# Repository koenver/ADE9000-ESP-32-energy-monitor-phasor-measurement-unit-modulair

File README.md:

# **ADE9000 ESP-32 energy-monitor / phasor-measurement-unit modulair**<br/>

*Prototype version of an Energy Measurement / Phasor Measurement unit with modulair interface modules*<br/>

**Specs:**<br/>
* ESP-32 processor (with double SPI and multicore, multi-tasking) and Wifi<br/> 
* Galvanic seperation with ADUM chips <br/>
* ADE9000 3 phase Energy Measurement IC , version for CT (5VA) or <br/>
        rogowski (0.1mV/A), 8kHz wavebuffering , harmonics analyses and <br/>
        event processing for 50Hz , 230V 3 phase Energy systems <br/>
* Module 1 slot: 485 interface / lorawan 868 Mhz/ Ethernet lan8720 (waveshare)<br/>
        
* Module 2 slot: Ublox GPS / DS3232 RTC<br/> 
* Expansion board: 485 interface, 2x 24lc512, mcp23017, ds2482, mcp4725,BME680<br/> 
        so 4 DI (opto), 4 DO (opto), 1-wire , temp, humidity, voc, air-pressure, <br/>
	AD en DA inputs and extra flash <br/>
* Optional I2C display  (SED1306 or H35B-I)<br/>
* future development:  security TLS1.3, module 2 with NB-Iot-LTE-M (Ublox)<br/> 
* Arduino IDE , in RTOS , C++ Language <br/>
<br/>

#### *Now in testing phase -> so only use parts which I confirmed status tested*<br/>
#### *better wait till new PCB's are published, instead of using the manual re-wiring*<br/>
*Software will be open source. (New) soft- and hardware which is based on this*<br/> 
*project and used by others, have the obligation of open source publishing*<br/> 
*at Github*<br/>

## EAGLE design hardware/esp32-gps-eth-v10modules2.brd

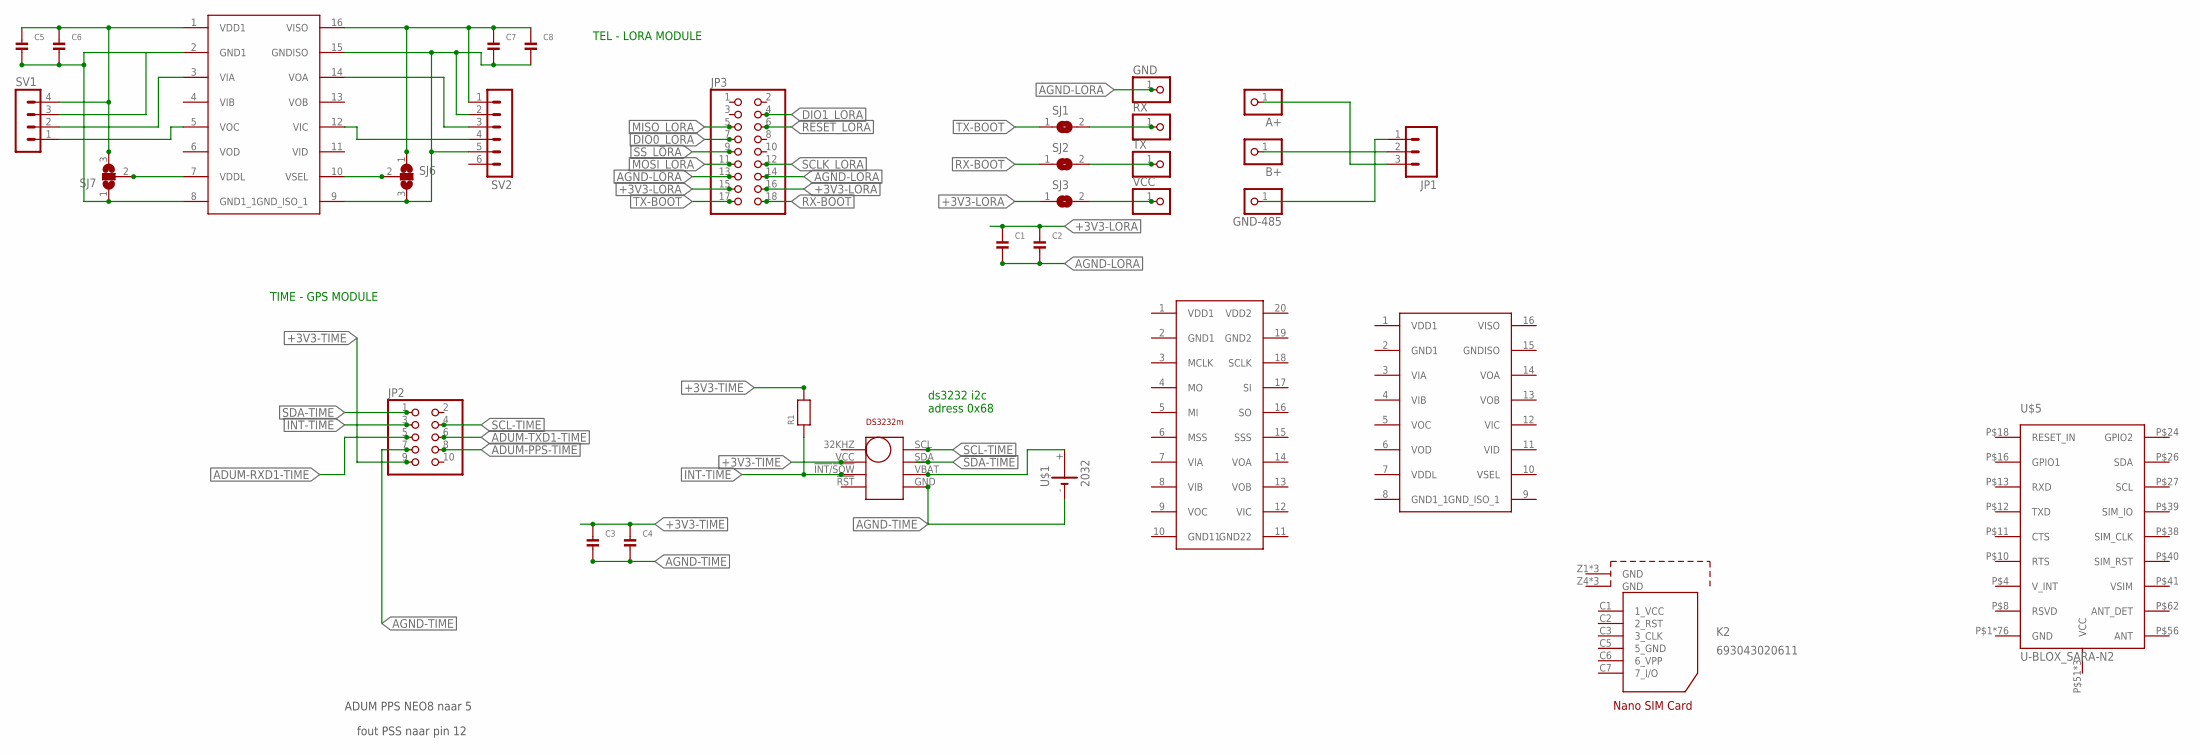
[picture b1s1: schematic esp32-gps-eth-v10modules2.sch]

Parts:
A+: PINHD-1X1CB; 1X01-CLEANBIG
ADUM4151: ADUM4151; SOIC20R
B+: PINHD-1X1CB; 1X01-CLEANBIG
C1, C2, C3, C4, C5, C6, C7, C8: CAP_CERAMIC0805; 0805
GND: PINHD-1X1CB; 1X01-CLEANBIG
GND-485: PINHD-1X1CB; 1X01-CLEANBIG
JP1: M03SCREW; SCREWTERMINAL-3.5MM-3
JP2: PINHD-2X5/90; 2X05/90
JP3: PINHD-2X9/90; 2X09/90
K2: 693043020611
R1: RESISTOR0805; 0805
RX: PINHD-1X1CB; 1X01-CLEANBIG
SJ1, SJ2, SJ3: SOLDERJUMPERREFLOW; SOLDERJUMPER_REFLOW
SJ6, SJ7: SJ2W; SJ_2
SV1: MA04-1
SV2: MA06-1
TX: PINHD-1X1CB; 1X01-CLEANBIG
U$1: 2032; KZH20SMD
U$2, U$3: ADUM6402; SOIC16R
U$4: DS3232M; SOIC8
U$5: U-BLOX_SARA-N2; SARA-N2
VCC: PINHD-1X1CB; 1X01-CLEANBIG

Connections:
+3V3-LORA: C1.1, C2.1, JP3.15, JP3.16, SJ3.1
+3V3-TIME: C3.1, C4.1, JP2.9, R1.2, U$4.VCC
ADUM-PPS-TIME: JP2.8
ADUM-RXD1-TIME: JP2.5
ADUM-TXD1-TIME: JP2.6
AGND-LORA: C1.2, C2.2, GND.1, JP3.13, JP3.14
AGND-TIME: C3.2, C4.2, JP2.7, U$1.-, U$4.GND
DIO0_LORA: JP3.7
DIO1_LORA: JP3.4
GND: U$5.P$1 (GND), U$5.P$2 (GND), U$5.P$3 (GND), U$5.P$5 (GND), U$5.P$6 (GND), U$5.P$7 (GND), U$5.P$9 (GND), U$5.P$14 (GND), U$5.P$15 (GND), U$5.P$17 (GND), U$5.P$19 (GND), U$5.P$20 (GND), U$5.P$21 (GND), U$5.P$22 (GND), U$5.P$23 (GND), U$5.P$25 (GND), U$5.P$28 (GND), U$5.P$29 (GND), U$5.P$30 (GND), U$5.P$31 (GND), U$5.P$32 (GND), U$5.P$33 (GND), U$5.P$34 (GND), U$5.P$35 (GND), U$5.P$36 (GND), U$5.P$37 (GND), U$5.P$42 (GND), U$5.P$43 (GND), U$5.P$44 (GND), U$5.P$45 (GND), U$5.P$46 (GND), U$5.P$47 (GND), U$5.P$48 (GND), U$5.P$49 (GND), U$5.P$50 (GND), U$5.P$54 (GND), U$5.P$55 (GND), U$5.P$57 (GND), U$5.P$58 (GND), U$5.P$59 (GND), U$5.P$60 (GND), U$5.P$61 (GND), U$5.P$63 (GND), U$5.P$64 (GND), U$5.P$65 (GND), U$5.P$66 (GND), U$5.P$67 (GND), U$5.P$68 (GND), U$5.P$69 (GND), U$5.P$70 (GND), U$5.P$71 (GND), U$5.P$72 (GND), U$5.P$73 (GND), U$5.P$74 (GND), U$5.P$75 (GND), U$5.P$76 (GND), U$5.P$77 (GND), U$5.P$78 (GND), U$5.P$79 (GND), U$5.P$80 (GND), U$5.P$81 (GND), U$5.P$82 (GND), U$5.P$83 (GND), U$5.P$84 (GND), U$5.P$85 (GND), U$5.P$86 (GND), U$5.P$87 (GND), U$5.P$88 (GND), U$5.P$89 (GND), U$5.P$90 (GND), U$5.P$91 (GND), U$5.P$92 (GND), U$5.P$93 (GND), U$5.P$94 (GND), U$5.P$95 (GND), U$5.P$96 (GND)
GND-PROG1: C5.2, C6.2, SJ7.1, U$3.8 (GND1_1)
GND-PROG2: C7.2, C8.2, SJ6.3, SV2.2, SV2.5, U$3.9 (GND_ISO_1), U$3.15 (GNDISO)
INT-TIME: JP2.3, R1.1, U$4.!INT/!!SQW
MISO_LORA: JP3.5
MOSI_LORA: JP3.11
unnamed: A+.1, JP1.3
unnamed: B+.1, JP1.2
unnamed: GND-485.1, JP1.1
unnamed: RX.1, SJ1.2
unnamed: U$1.+, U$4.VBAT
unnamed: SJ2.2, TX.1
unnamed: SJ3.2, VCC.1
unnamed: SV1.1, U$3.5 (VOC)
unnamed: SV1.3, U$3.2 (GND1)
unnamed: SV1.2, U$3.3 (VIA)
unnamed: SV2.3, U$3.14 (VOA)
unnamed: SV2.4, U$3.12 (VIC)
unnamed: SJ7.2, U$3.7 (VDDL)
unnamed: SJ6.2, U$3.10 (VSEL)
RESET_LORA: JP3.6
RX-BOOT: JP3.18, SJ2.1
SCL-TIME: JP2.4, U$4.SCL
SCLK_LORA: JP3.12
SDA-TIME: JP2.1, U$4.SDA
SS_LORA: JP3.9
TX-BOOT: JP3.17, SJ1.1
VCC: U$5.P$51 (VCC), U$5.P$52 (VCC), U$5.P$53 (VCC)
VCC2-PROG: C7.1, C8.1, SJ6.1, SV2.1, U$3.16 (VISO)
VCC-PROG: C5.1, C6.1, SJ7.3, SV1.4, U$3.1 (VDD1)

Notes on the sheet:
ADUM PPS NEO8 naar 5
fout PSS naar pin 12
ds3232 i2c adress 0x68
TEL - LORA MODULE
TIME - GPS MODULE

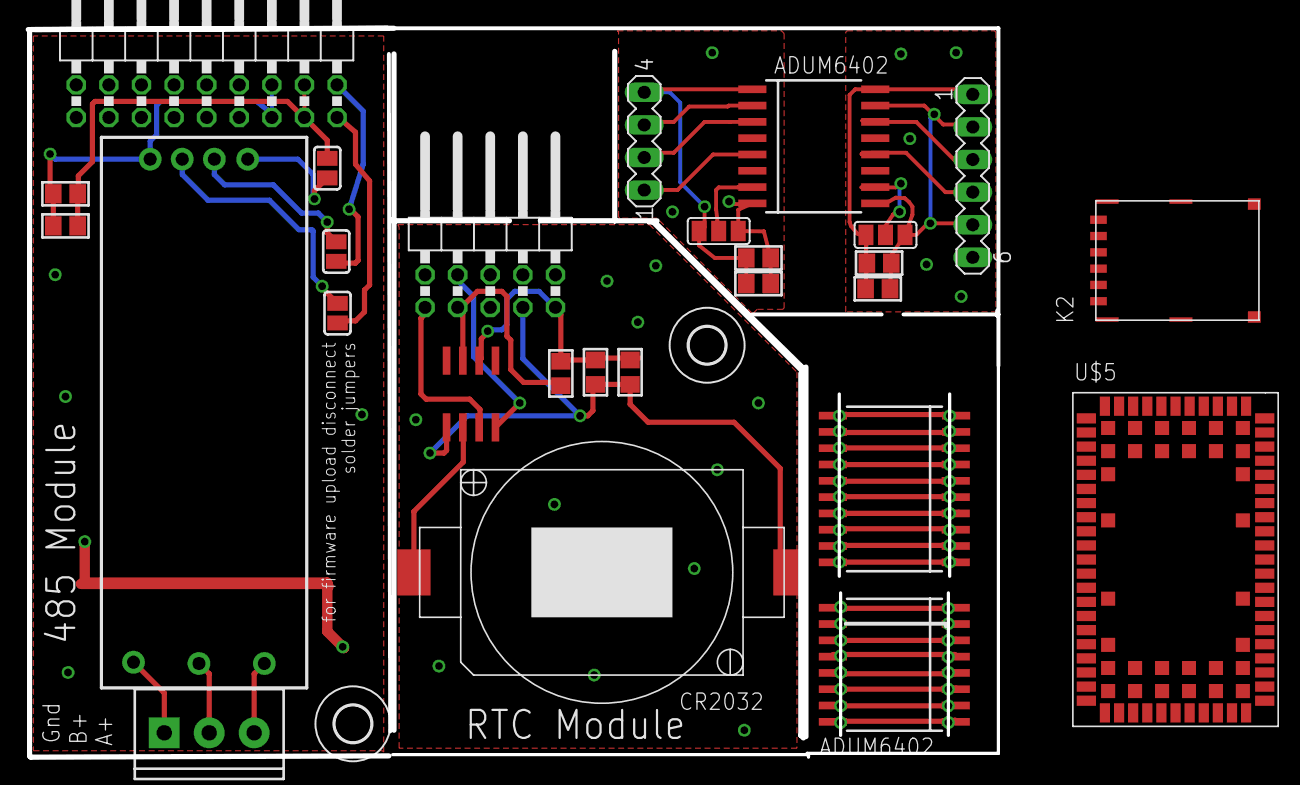
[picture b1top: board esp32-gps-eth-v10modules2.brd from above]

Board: 2 copper layers, 75.6 x 56.8 mm, 35 parts (0 on the bottom side), 29 nets.

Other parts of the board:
U$7, U$8: 2,8

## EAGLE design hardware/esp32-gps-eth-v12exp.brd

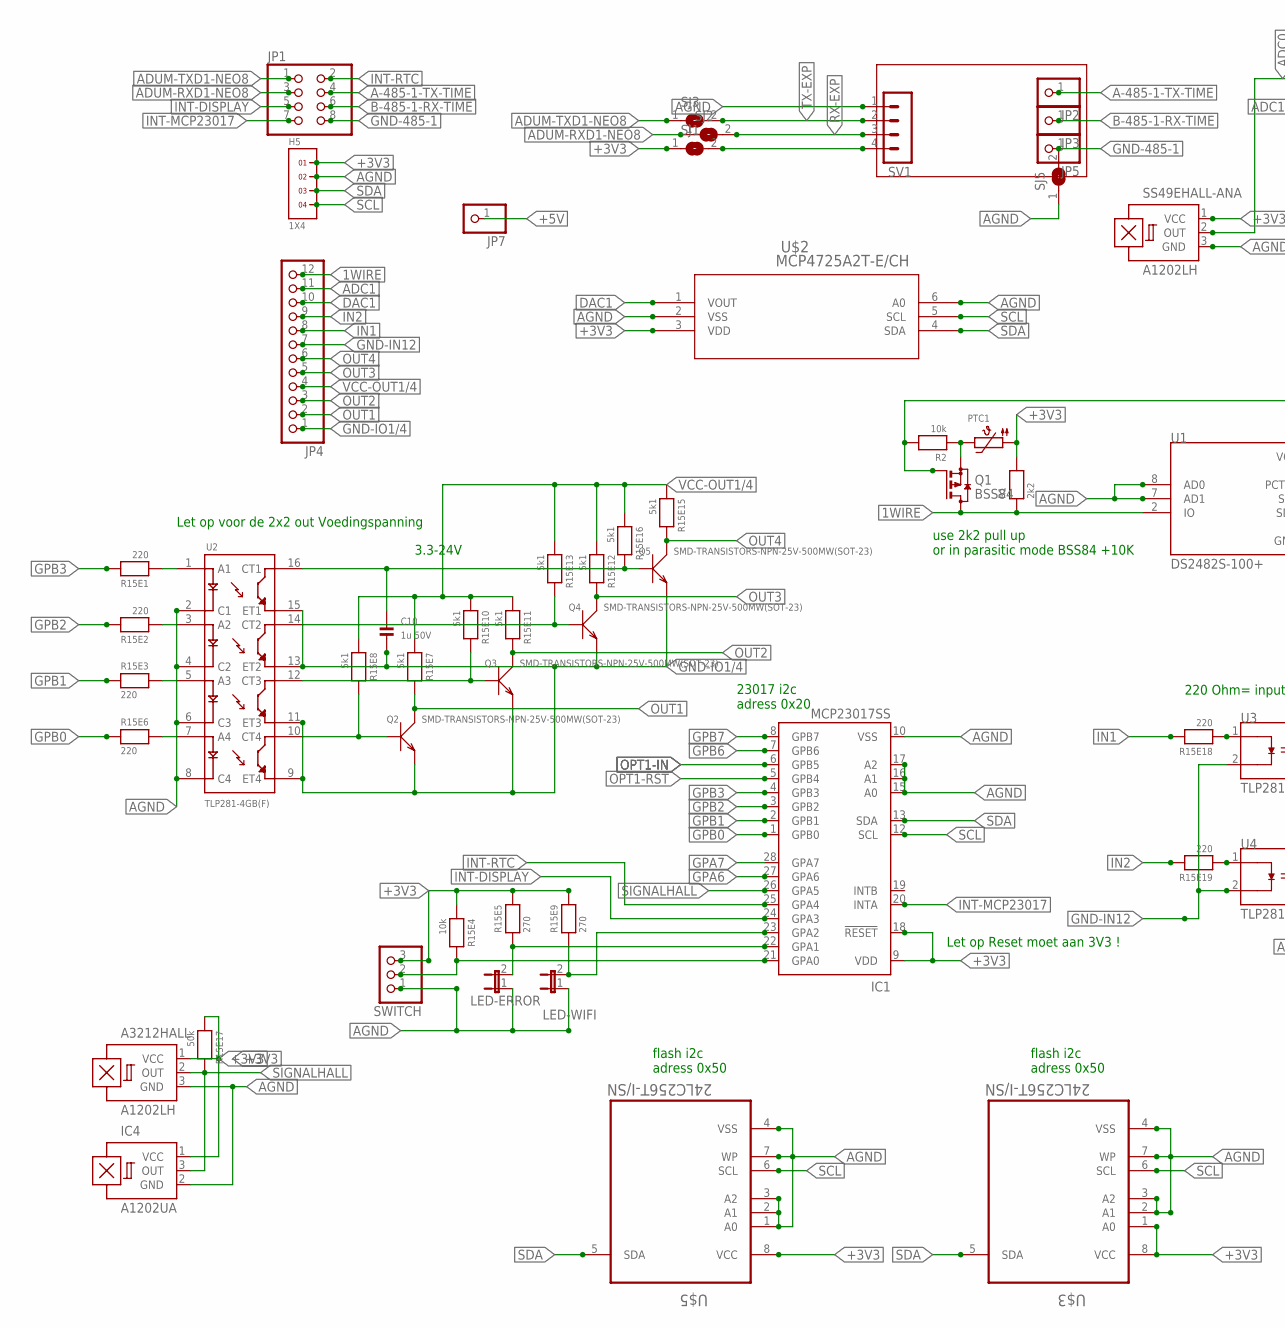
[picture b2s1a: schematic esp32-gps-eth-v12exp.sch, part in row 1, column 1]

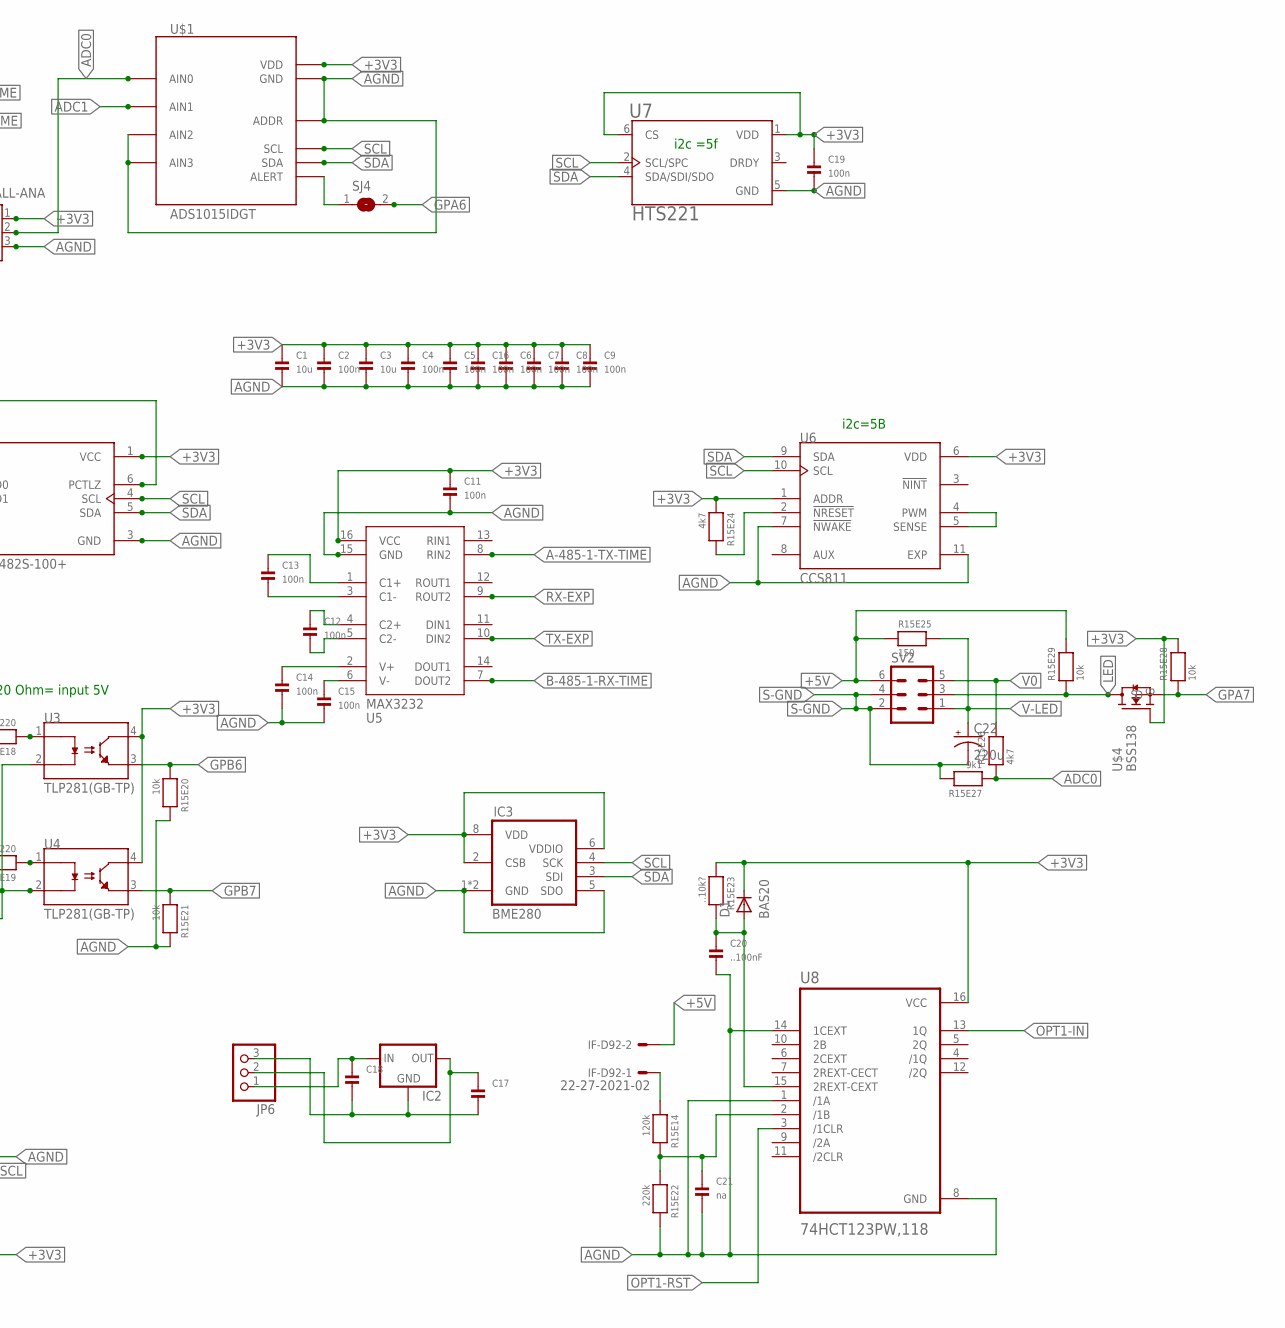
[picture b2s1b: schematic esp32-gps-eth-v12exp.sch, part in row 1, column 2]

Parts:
A3212HALL: A1202LH; SOT23-W
C1, C3: 10u; 0805
C2, C4, C5, C6, C7, C8, C9, C11, C12, C13, C14, C15, C16, C19: 100n; 0805
C10: 1u 50V; 0805
C17, C18: CAP_CERAMIC0805; 0805
C20: ..100nF; 0805
C21: na; 0805
C22: 220u; 153CLV-0605
D1: BAS20; SOT23
H5: 1X4
IC1: MCP23017SS; SSOP28
IC2: LM1117TO263; TO263
IC3: BME280
IC4: A1202UA; SIP3-UA
IF-D92: 22-27-2021-02; 6410-02
JP1: PINHD-2X4; 2X04
JP2, JP3, JP5, JP7: PINHD-1X1; 1X01
JP4: PINHD-1X12; 1X12
JP6: PINHD-1X3; 1X03
LED-ERROR: JP1E; JP1
LED-WIFI: JP1E; JP1
PTC1: PTC1206; 1206
Q1: BSS84; SOT23
Q2, Q3, Q4, Q5: SMD-TRANSISTORS-NPN-25V-500MW(SOT-23); SOT-23
R1: 2k2; 0805
R2: 10k; 0805
R15E1, R15E2, R15E3, R15E6, R15E18, R15E19: 220; _0805
R15E4, R15E20, R15E21, R15E28, R15E29: 10k; _0805
R15E5, R15E9: 270; _0805
R15E7, R15E8, R15E10, R15E11, R15E12, R15E13, R15E15, R15E16: 5k1; _0805
R15E14: 120k; _0805
R15E17: 50k; _0805
R15E22: 220k; _0805
R15E23: ..10k?; _0805
R15E24, R15E26: 4k7; _0805
R15E25: 150; _0805
R15E27: 9k1; _0805
SJ1, SJ2, SJ3, SJ4, SJ5: SJ
SS49EHALL-ANA: A1202LH; SOT23-W
SV1: MA04-1
SV2: MA03-2
SWITCH: PINHD-1X3; 1X03
U1: DS2482S-100+; SOIC127P600X175-8N
U2: TLP281-4GB(F); SOIC127P700X210-16N
U3, U4: TLP281(GB-TP); SOIC127P700X210-4N
U5: MAX3232; SO16
U6: CCS811; SON60P270X400X110-11N
U7: HTS221; XDCR_HTS221
U8: 74HCT123PW,118; SOP65P640X110-16N
U$1: ADS1015IDGT; MSOP10_0.5
U$2: MCP4725A2T-E/CH; SOT-23-6_MC
U$3, U$5: 24LC256T-I/SN; SOIC127P600X175-8N
U$4: BSS138

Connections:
1WIRE: JP4.12, Q1.3 (D), R1.1, U1.2 (IO)
5VIN: C18.1, IC2.3 (IN), JP6.1
+3V3: A3212HALL.1 (VCC), C1.1, C2.1, C3.1, C4.1, C5.1, C6.1, C7.1, C8.1, C9.1, C11.1, C16.1, C19.1, D1.3 (K), H5.1, IC1.9 (VDD), IC1.18 (!RESET), IC3.2 (CSB), IC3.6 (VDDIO), IC3.8 (VDD), IC4.1 (VCC), PTC1.1, R1.2, R15E4.1, R15E5.2, R15E9.2, R15E17.1, R15E23.1, R15E24.1, R15E28.2, SJ1.1, SS49EHALL-ANA.1 (VCC), SWITCH.3, U1.1 (VCC), U3.4 (COLLECTOR), U4.4 (COLLECTOR), U5.16 (VCC), U6.1 (ADDR), U6.6 (VDD), U7.1 (VDD), U7.6 (CS), U8.16 (VCC), U$1.8 (VDD), U$2.3 (VDD), U$3.1 (A0), U$3.8 (VCC), U$4.G, U$5.8 (VCC)
+5V: IF-D92.2, JP7.1, R15E25.1, R15E29.2, SV2.6
A-485-1-TX-TIME: JP1.4, JP2.1, U5.8 (RIN2)
ADC0: R15E26.1, R15E27.1, SS49EHALL-ANA.2 (OUT), U$1.4 (AIN0)
ADC1: JP4.11, U$1.5 (AIN1)
ADUM-RXD1-NEO8: JP1.3, SJ2.1
ADUM-TXD1-NEO8: JP1.1, SJ3.1
AGND: A3212HALL.3 (GND), C1.2, C2.2, C3.2, C4.2, C5.2, C6.2, C7.2, C8.2, C9.2, C11.2, C14.2, C15.2, C16.2, C19.2, C20.2, C21.2, H5.2, IC1.10 (VSS), IC1.15 (A0), IC1.16 (A1), IC1.17 (A2), IC3.1 (GND), IC3.5 (SDO), IC3.7 (GND), IC4.2 (GND), LED-ERROR.1, LED-WIFI.1, R15E20.2, R15E21.2, R15E22.2, SJ5.1, SS49EHALL-ANA.3 (GND), SV1.1, SWITCH.1, U1.3 (GND), U1.7 (AD1), U1.8 (AD0), U2.2 (C1), U2.4 (C2), U2.6 (C3), U2.8 (C4), U5.15 (GND), U6.7 (!NWAKE), U6.11 (EXP), U7.5 (GND), U8.1 (/1A), U8.8 (GND), U8.14 (1CEXT), U$1.1 (ADDR), U$1.3 (GND), U$1.6 (AIN2), U$1.7 (AIN3), U$2.2 (VSS), U$2.6 (A0), U$3.2 (A1), U$3.3 (A2), U$3.4 (VSS), U$3.7 (WP), U$5.1 (A0), U$5.2 (A1), U$5.3 (A2), U$5.4 (VSS), U$5.7 (WP)
B-485-1-RX-TIME: JP1.6, JP3.1, U5.7 (DOUT2)
DAC1: JP4.10, U$2.1 (VOUT)
GND-485-1: JP1.8, JP5.1, SJ5.2
GND-IN: C17.2, C18.2, IC2.1 (GND), JP6.3
GND-IN12: JP4.7, U3.2 (CATHODE), U4.2 (CATHODE)
GND-IO1/4: C10.2, JP4.1, Q2.2 (E), Q3.2 (E), Q4.2 (E), Q5.2 (E), U2.9 (ET4), U2.11 (ET3), U2.13 (ET2), U2.15 (ET1)
GPA6: IC1.27 (GPA6), SJ4.2
GPA7: IC1.28 (GPA7), R15E28.1, U$4.S
GPB0: IC1.1 (GPB0), R15E6.1
GPB1: IC1.2 (GPB1), R15E3.1
GPB2: IC1.3 (GPB2), R15E2.2
GPB3: IC1.4 (GPB3), R15E1.2
GPB6: IC1.7 (GPB6), R15E20.1, U3.3 (EMITTER)
GPB7: IC1.8 (GPB7), R15E21.1, U4.3 (EMITTER)
IN1: JP4.8, R15E18.2
IN2: JP4.9, R15E19.2
INT-DISPLAY: IC1.24 (GPA3), JP1.5
INT-MCP23017: IC1.20 (INTA), JP1.7
INT-RTC: IC1.25 (GPA4), JP1.2
LED: R15E29.1, SV2.3, U$4.D
unnamed: PTC1.2, Q1.2 (S), R2.1
unnamed: C13.1, U5.1 (C1+)
unnamed: SJ1.2, SV1.4
unnamed: Q1.1 (G), R2.2, U1.6 (PCTLZ)
unnamed: Q2.1 (B), R15E8.2, U2.10 (CT4)
unnamed: R15E2.1, U2.3 (A2)
unnamed: R15E1.1, U2.1 (A1)
unnamed: IC1.21 (GPA0), R15E4.2, SWITCH.2
unnamed: IC1.22 (GPA1), LED-ERROR.2, R15E5.1
unnamed: IC1.23 (GPA2), LED-WIFI.2, R15E9.1
unnamed: R15E3.2, U2.5 (A3)
unnamed: R15E6.2, U2.7 (A4)
unnamed: Q3.1 (B), R15E10.2, U2.12 (CT3)
unnamed: Q4.1 (B), R15E13.2, U2.14 (CT2)
unnamed: C10.1, Q5.1 (B), R15E16.2, U2.16 (CT1)
unnamed: C13.2, U5.3 (C1-)
unnamed: R15E19.1, U4.1 (ANODE)
unnamed: R15E18.1, U3.1 (ANODE)
unnamed: SJ4.1, U$1.2 (ALERT)
unnamed: C12.1, U5.4 (C2+)
unnamed: C12.2, U5.5 (C2-)
unnamed: C14.1, U5.2 (V+)
unnamed: C15.1, U5.6 (V-)
unnamed: R15E24.2, U6.2 (!NRESET)
unnamed: IF-D92.1, R15E14.1
unnamed: C21.1, R15E14.2, R15E22.1, U8.2 (/1B)
unnamed: U6.4 (PWM), U6.5 (SENSE)
unnamed: C20.1, D1.1 (A), R15E23.2, U8.15 (2REXT-CEXT)
OPT1-IN: IC1.6 (GPB5), U8.13 (1Q)
OPT1-RST: IC1.5 (GPB4), U8.3 (/1CLR)
OUT1: JP4.2, Q2.3 (C), R15E7.2
OUT2: JP4.3, Q3.3 (C), R15E11.2
OUT3: JP4.5, Q4.3 (C), R15E12.2
OUT4: JP4.6, Q5.3 (C), R15E15.2
RX-EXP: SJ2.2, SV1.3, U5.9 (ROUT2)
S-GND: C22.-, R15E27.2, SV2.2, SV2.4
SCL: H5.4, IC1.12 (SCL), IC3.4 (SCK), U1.4 (SCL), U6.10 (SCL), U7.2 (SCL/SPC), U$1.10 (SCL), U$2.5 (SCL), U$3.6 (SCL), U$5.6 (SCL)
SDA: H5.3, IC1.13 (SDA), IC3.3 (SDI), U1.5 (SDA), U6.9 (SDA), U7.4 (SDA/SDI/SDO), U$1.9 (SDA), U$2.4 (SDA), U$3.5 (SDA), U$5.5 (SDA)
SIGNALHALL: A3212HALL.2 (OUT), IC1.26 (GPA5), IC4.3 (OUT), R15E17.2
TX-EXP: SJ3.2, SV1.2, U5.10 (DIN2)
V0: R15E26.2, SV2.5
V-LED: C22.+, R15E25.2, SV2.1
VCC-OUT1/4: JP4.4, R15E7.1, R15E8.1, R15E10.1, R15E11.1, R15E12.1, R15E13.1, R15E15.1, R15E16.1
VOUT: C17.1, IC2.2 (OUT), JP6.2

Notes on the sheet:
23017 i2c adress 0x20
flash i2c adress 0x50
use 2k2 pull up or in parasitic mode BSS84 +10K
3.3-24V
Let op voor de 2x2 out Voedingspanning
220 Ohm= input 5V
i2c =5f
i2c=5B
Let op Reset moet aan 3V3 !

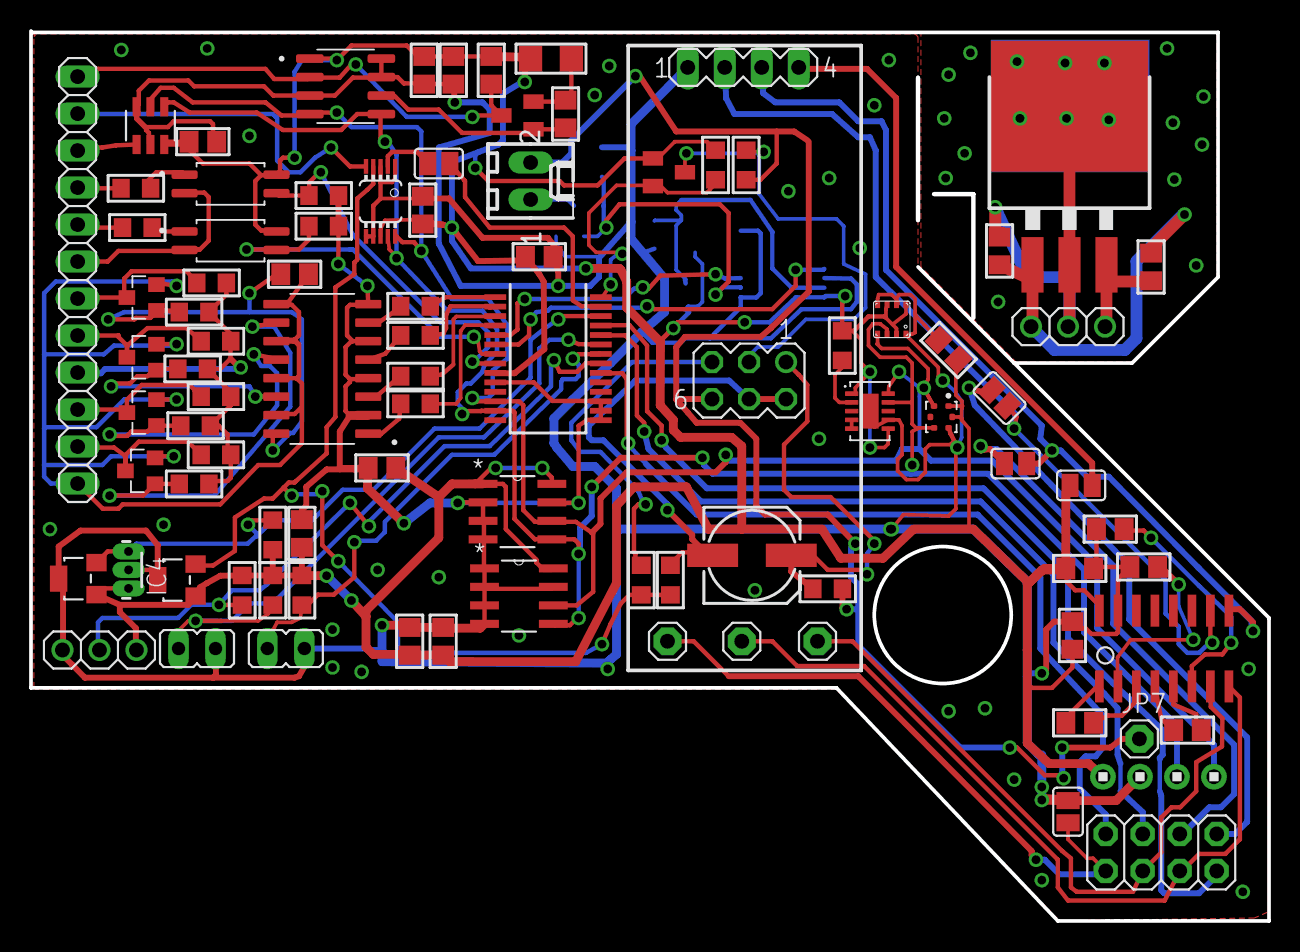
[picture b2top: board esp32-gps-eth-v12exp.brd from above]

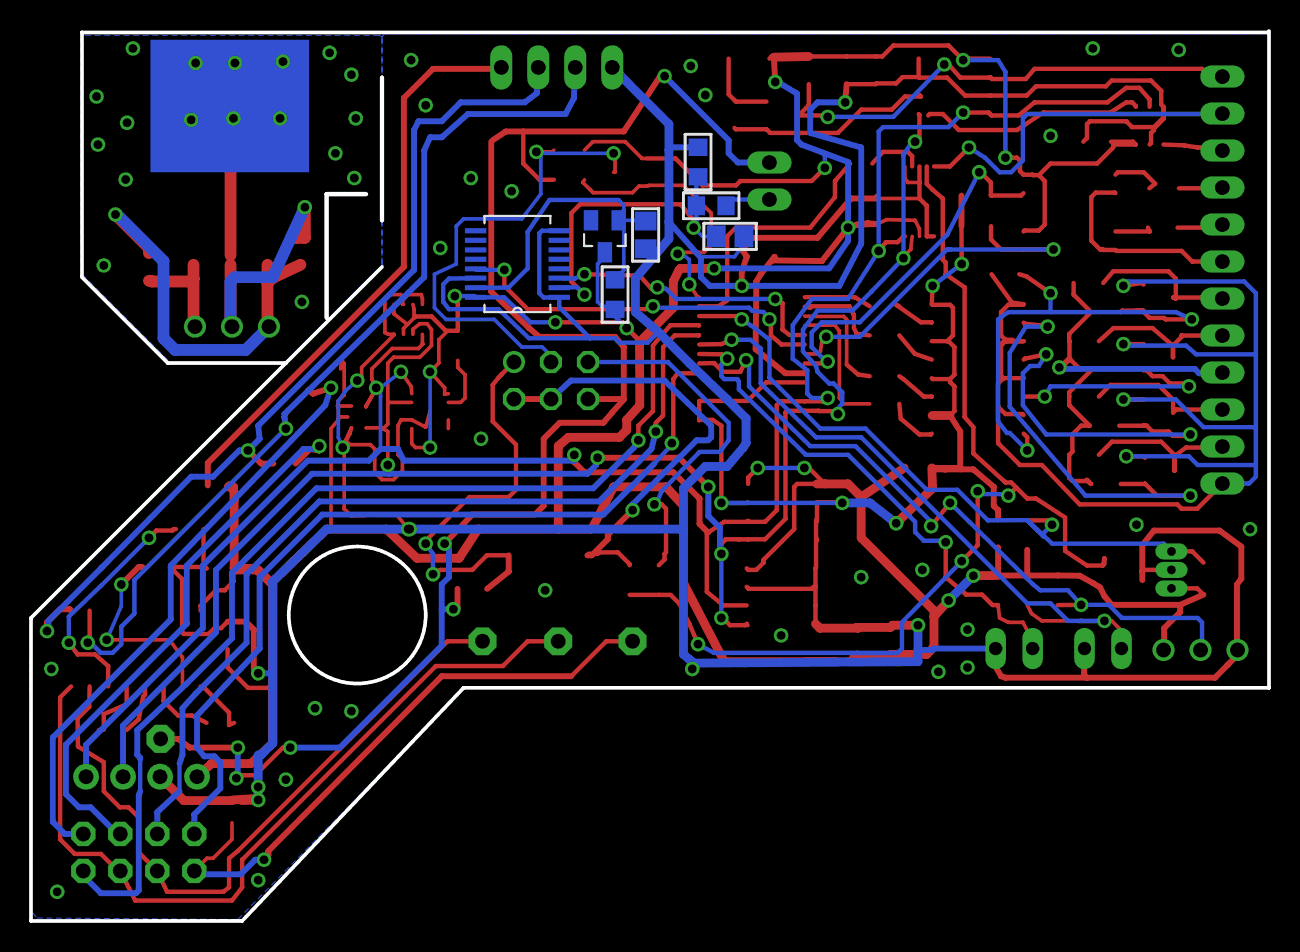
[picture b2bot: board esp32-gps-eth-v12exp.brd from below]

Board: 2 copper layers, 85.0 x 61.1 mm, 98 parts (7 on the bottom side), 74 nets.

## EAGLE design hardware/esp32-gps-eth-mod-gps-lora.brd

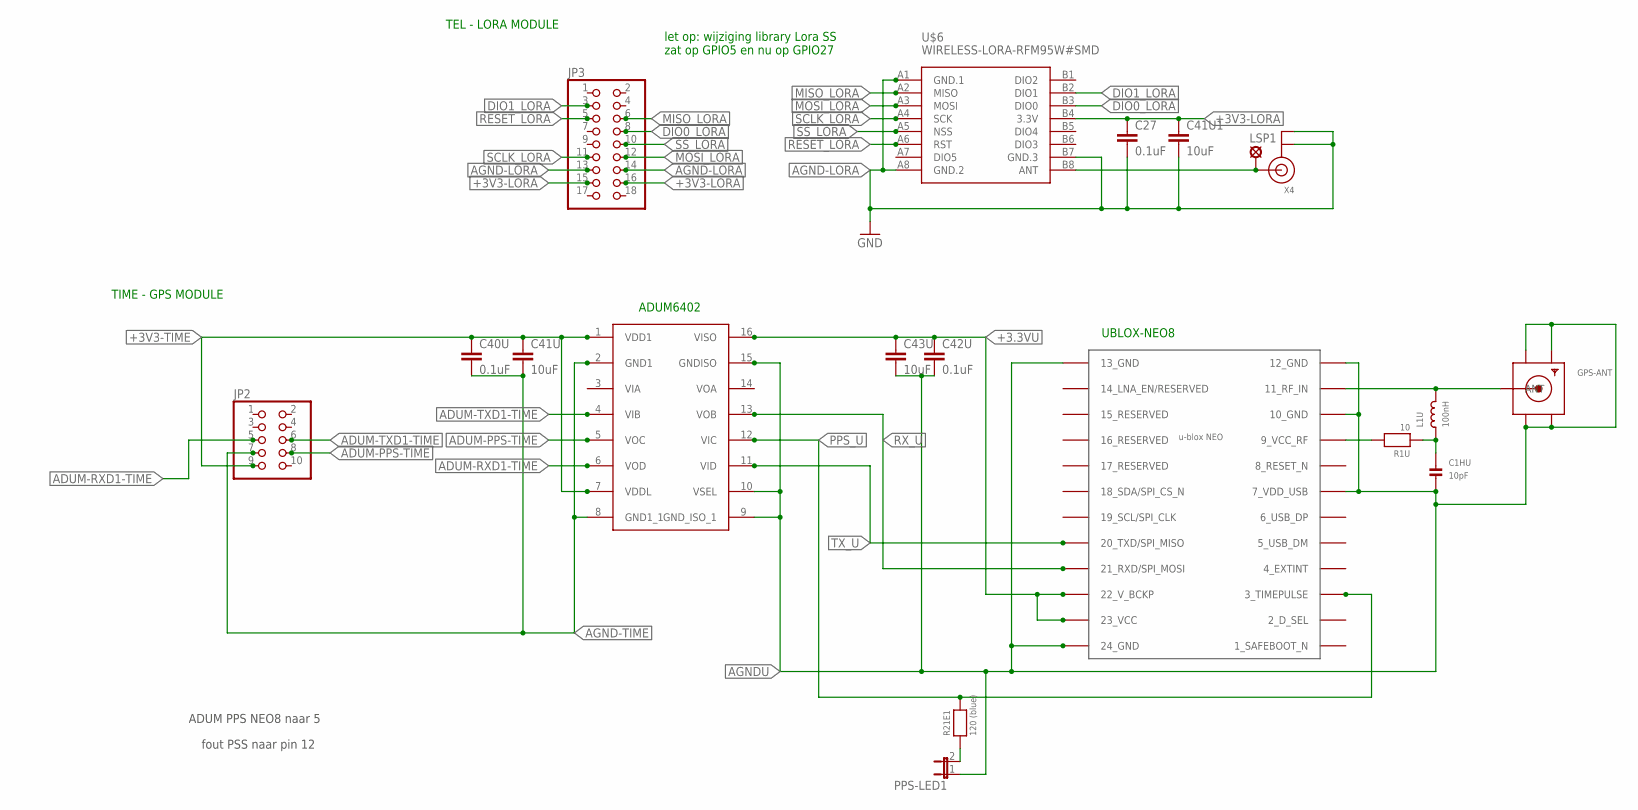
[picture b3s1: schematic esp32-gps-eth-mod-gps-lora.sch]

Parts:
C1HU: 10pF; _0805
C27, C40U, C42U: 0.1uF; C0805
C41U, C41U1, C43U: 10uF; C0805
GPS-ANT: SMACONNECTOR; SMA90_DIP
JP2: PINHD-2X5/90; 2X05/90
JP3: PINHD-2X9/90; 2X09/90
L1U: 100nH; 0805
LSP1: LSP10
PPS-LED1: JP1E; JP1
R1U: 10; _0805
R21E1: 120 (blue); _0805
U$2: ADUM6402; SOIC16R
U$6: WIRELESS-LORA-RFM95W#SMD
UBLOX-NEO8: NEO-M8
X4: ANTENNA_U.FL; U.FL

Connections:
+3.3VU: C42U.1, C43U.1, U$2.16 (VISO), UBLOX-NEO8.22 (22_V_BCKP), UBLOX-NEO8.23 (23_VCC)
+3V3-LORA: C27.1, C41U1.1, JP3.15, JP3.16, U$6.B4 (3.3V)
+3V3-TIME: C40U.1, C41U.1, JP2.9, U$2.1 (VDD1), U$2.7 (VDDL)
ADUM-PPS-TIME: JP2.8, U$2.5 (VOC)
ADUM-RXD1-TIME: JP2.5, U$2.6 (VOD)
ADUM-TXD1-TIME: JP2.6, U$2.4 (VIB)
AGND-LORA: C27.2, C41U1.2, JP3.13, JP3.14, U$6.A1 (GND.1), U$6.A8 (GND.2), U$6.B7 (GND.3), X4.1 (GND), X4.2 (GND)
AGND-TIME: C40U.2, C41U.2, JP2.7, U$2.2 (GND1), U$2.8 (GND1_1)
AGNDU: C1HU.2, C42U.2, C43U.2, GPS-ANT.GND1, GPS-ANT.GND2, GPS-ANT.GND3, GPS-ANT.GND4, PPS-LED1.1, U$2.9 (GND_ISO_1), U$2.10 (VSEL), U$2.15 (GNDISO), UBLOX-NEO8.7 (7_VDD_USB), UBLOX-NEO8.10 (10_GND), UBLOX-NEO8.12 (12_GND), UBLOX-NEO8.13 (13_GND), UBLOX-NEO8.24 (24_GND)
DIO0_LORA: JP3.8, U$6.B3 (DIO0)
DIO1_LORA: JP3.3, U$6.B2 (DIO1)
MISO_LORA: JP3.6, U$6.A2 (MISO)
MOSI_LORA: JP3.12, U$6.A3 (MOSI)
unnamed: PPS-LED1.2, R21E1.1
unnamed: R1U.2, UBLOX-NEO8.9 (9_VCC_RF)
unnamed: LSP1.MP, U$6.B8 (ANT), X4.3 (SIGNAL)
unnamed: C1HU.1, L1U.1, R1U.1
unnamed: GPS-ANT.ANTENNA (ANT), L1U.2, UBLOX-NEO8.11 (11_RF_IN)
PPS_U: R21E1.2, U$2.12 (VIC), UBLOX-NEO8.3 (3_TIMEPULSE)
RESET_LORA: JP3.5, U$6.A6 (RST)
RX_U: U$2.13 (VOB), UBLOX-NEO8.21 (21_RXD/SPI_MOSI)
SCLK_LORA: JP3.11, U$6.A4 (SCK)
SS_LORA: JP3.10, U$6.A5 (NSS)
TX_U: U$2.11 (VID), UBLOX-NEO8.20 (20_TXD/SPI_MISO)

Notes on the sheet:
ADUM6402
UBLOX-NEO8
ADUM PPS NEO8 naar 5
fout PSS naar pin 12
let op: wijziging library Lora SS zat op GPIO5 en nu op GPIO27
TEL - LORA MODULE
TIME - GPS MODULE

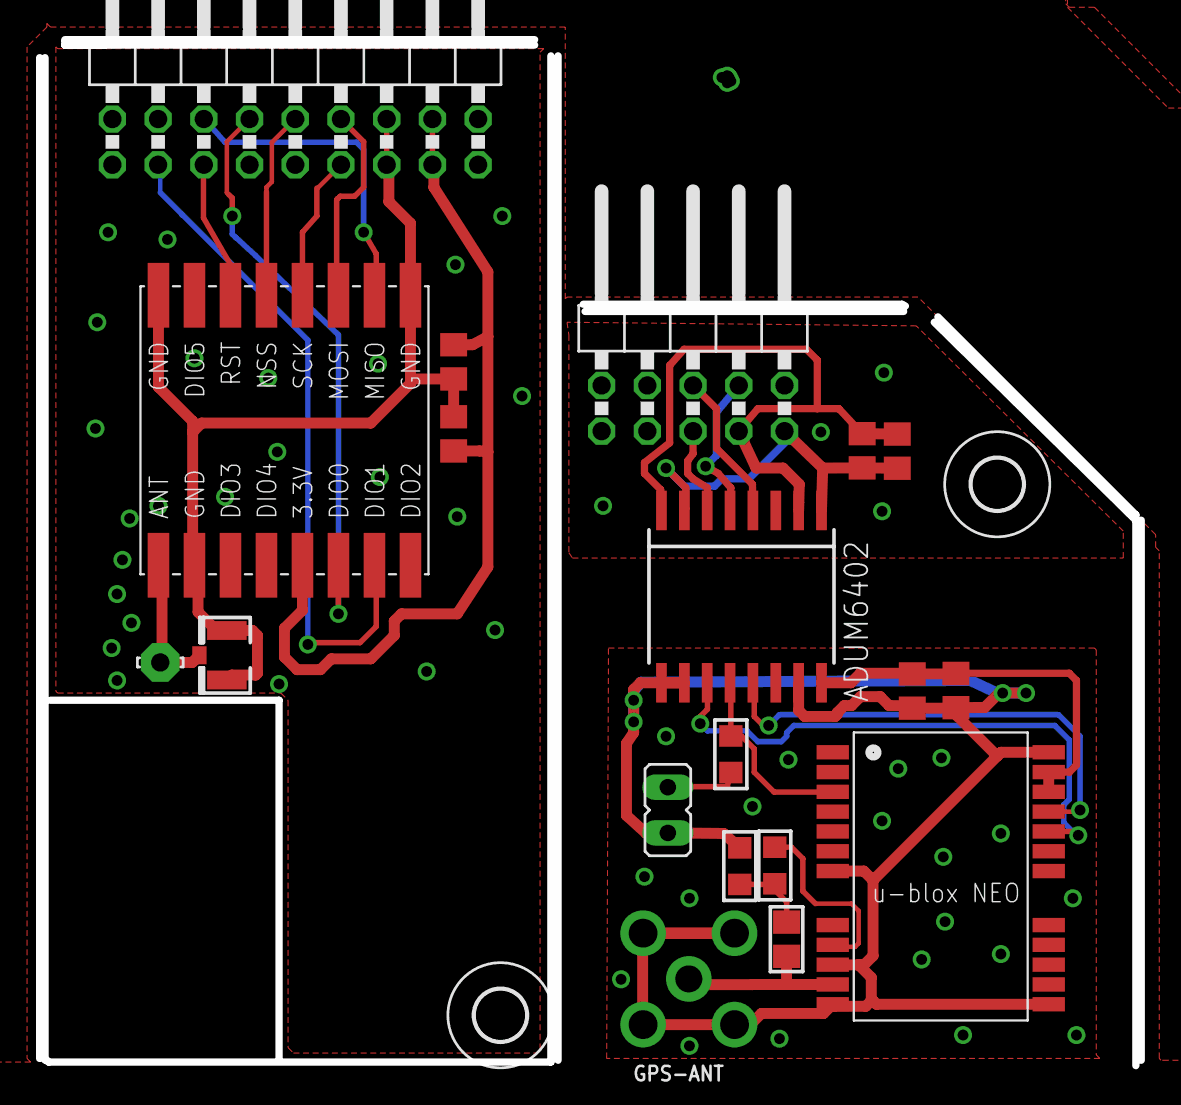
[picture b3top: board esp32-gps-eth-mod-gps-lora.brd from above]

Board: 2 copper layers, 61.2 x 57.0 mm, 21 parts (0 on the bottom side), 24 nets.

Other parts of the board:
U$7, U$8: 2,8

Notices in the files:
parts and their libraries:
microbuilder: This work is placed in the public domain, and may be freely used for commercial and non-commercial work with the following conditions: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
diy-modules: Released under the Creative Commons Attribution 4.0 International License: http://creativecommons.org/licenses/by/4.0
